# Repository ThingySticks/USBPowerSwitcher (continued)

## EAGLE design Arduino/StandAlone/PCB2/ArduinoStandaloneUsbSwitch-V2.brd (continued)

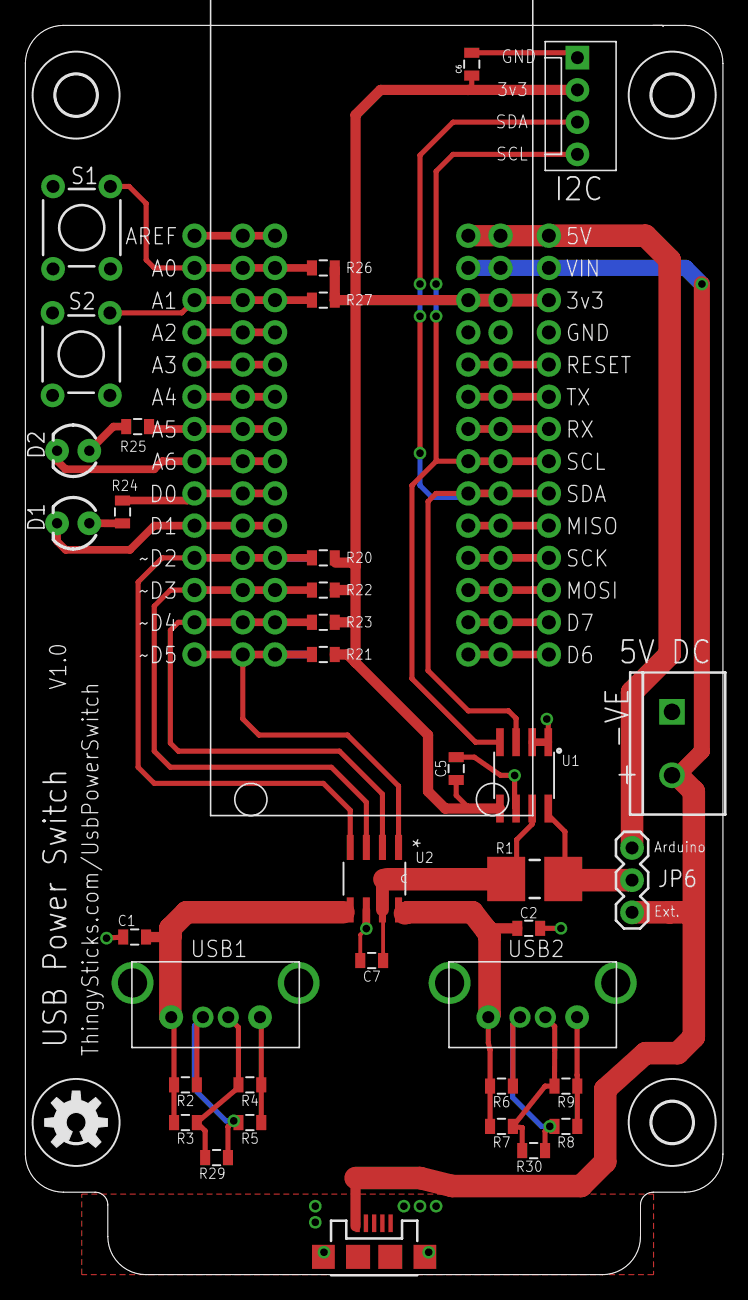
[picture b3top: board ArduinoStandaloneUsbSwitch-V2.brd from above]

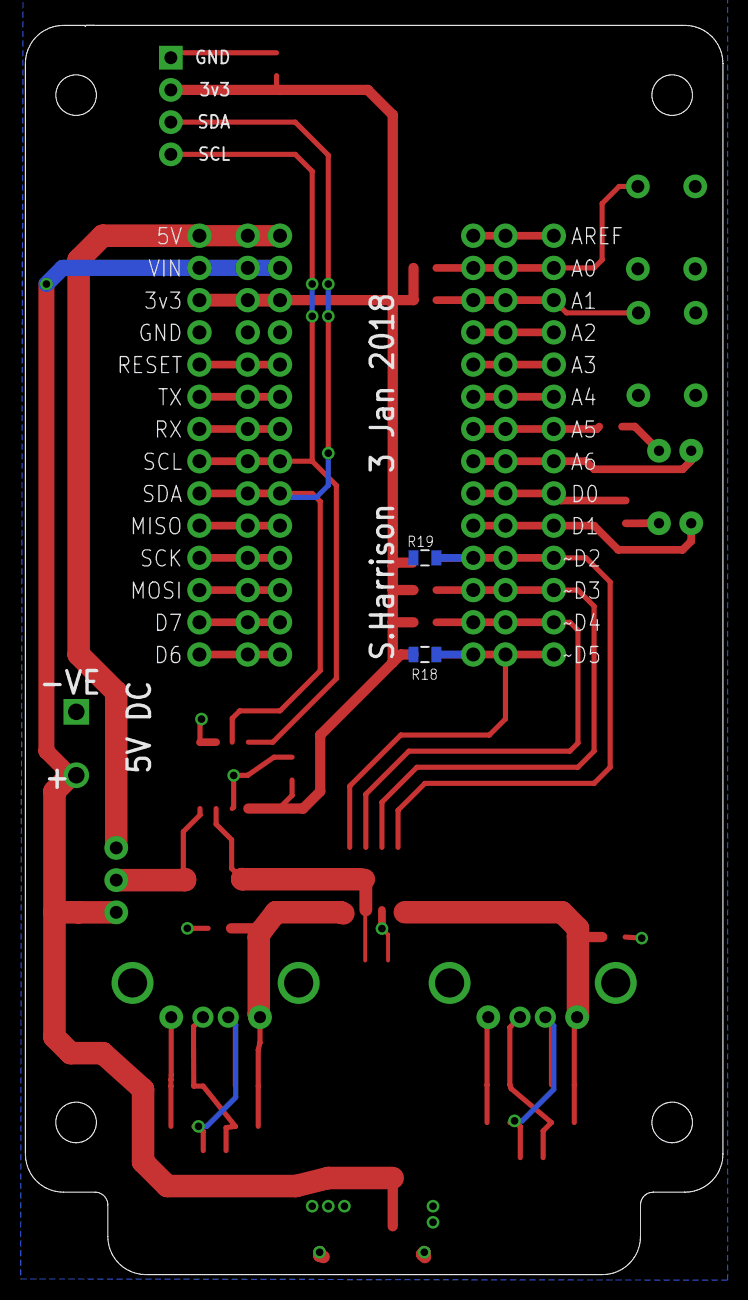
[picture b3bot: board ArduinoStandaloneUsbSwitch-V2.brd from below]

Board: 2 copper layers, 55.0 x 98.5 mm, 45 parts (2 on the bottom side), 38 nets.

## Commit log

2018-01-22 V1 of the "V2" board as made by DirtyPCBs.
    NOTE: USB sockets are the wrong way around!
2018-01-22 First version for a wall socket remove controlled outlet.
    USB socket polarity likely reversed!
2018-01-23 Added enclosure.
2018-01-23 Adding BOM
2018-01-23 First verion of s/w switching outlets and measuring current.
2018-01-23 Improved TFT display cutout.
2018-01-23 4 Port version of the switcher.
2018-01-23 Added gitignore
2018-01-23 Added image exports from first version sent to DirtyPCBs for 4 port switcher.
2018-01-29 Enclosure for 2 port USB switch.
2018-01-29 Start of firmware for alexa/tinamous control of the USB ports.
2018-01-29 Tidied up, added notes.
2018-02-13 Moved 2 port case into 2 port folder.
2018-02-13 Added component values during build.
2018-02-13 First pass at 4 port case.
2018-02-15 Seperated the lid to it's own scad file and folder.
2018-02-15 Added options for 4 port build for case openings and increased the opening for the terminal block.
    Removed lid code which is now standalong.
2018-02-15 Removed lid code which is now standalong.
2018-02-23 Implemented multiport switching to handle Alexa control
2018-02-23 Updated device values.
2018-02-23 LED spacer to hold the LED at the correct distance required for mounting in the case.
2018-02-23 Increased hole sized and added stoppers to stop the battery falling out.
2018-02-23 Split out the lid to it's own folder.
2018-02-24 BOM for 4 port switch
2018-02-24 Added readme ;-)
